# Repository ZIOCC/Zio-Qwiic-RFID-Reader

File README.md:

# Zio Qwiic RFID Reader (MFRC522)

> ###### About Zio
> Zio is a new line of open sourced, compact, and grid layout boards, fully integrated for Arduino and Qwiic ecosystem. Designed ideally for wearables, robotics, small-space limitations or other on the go projects. Check out other awesome Zio products [here](https://www.smart-prototyping.com/Zio)

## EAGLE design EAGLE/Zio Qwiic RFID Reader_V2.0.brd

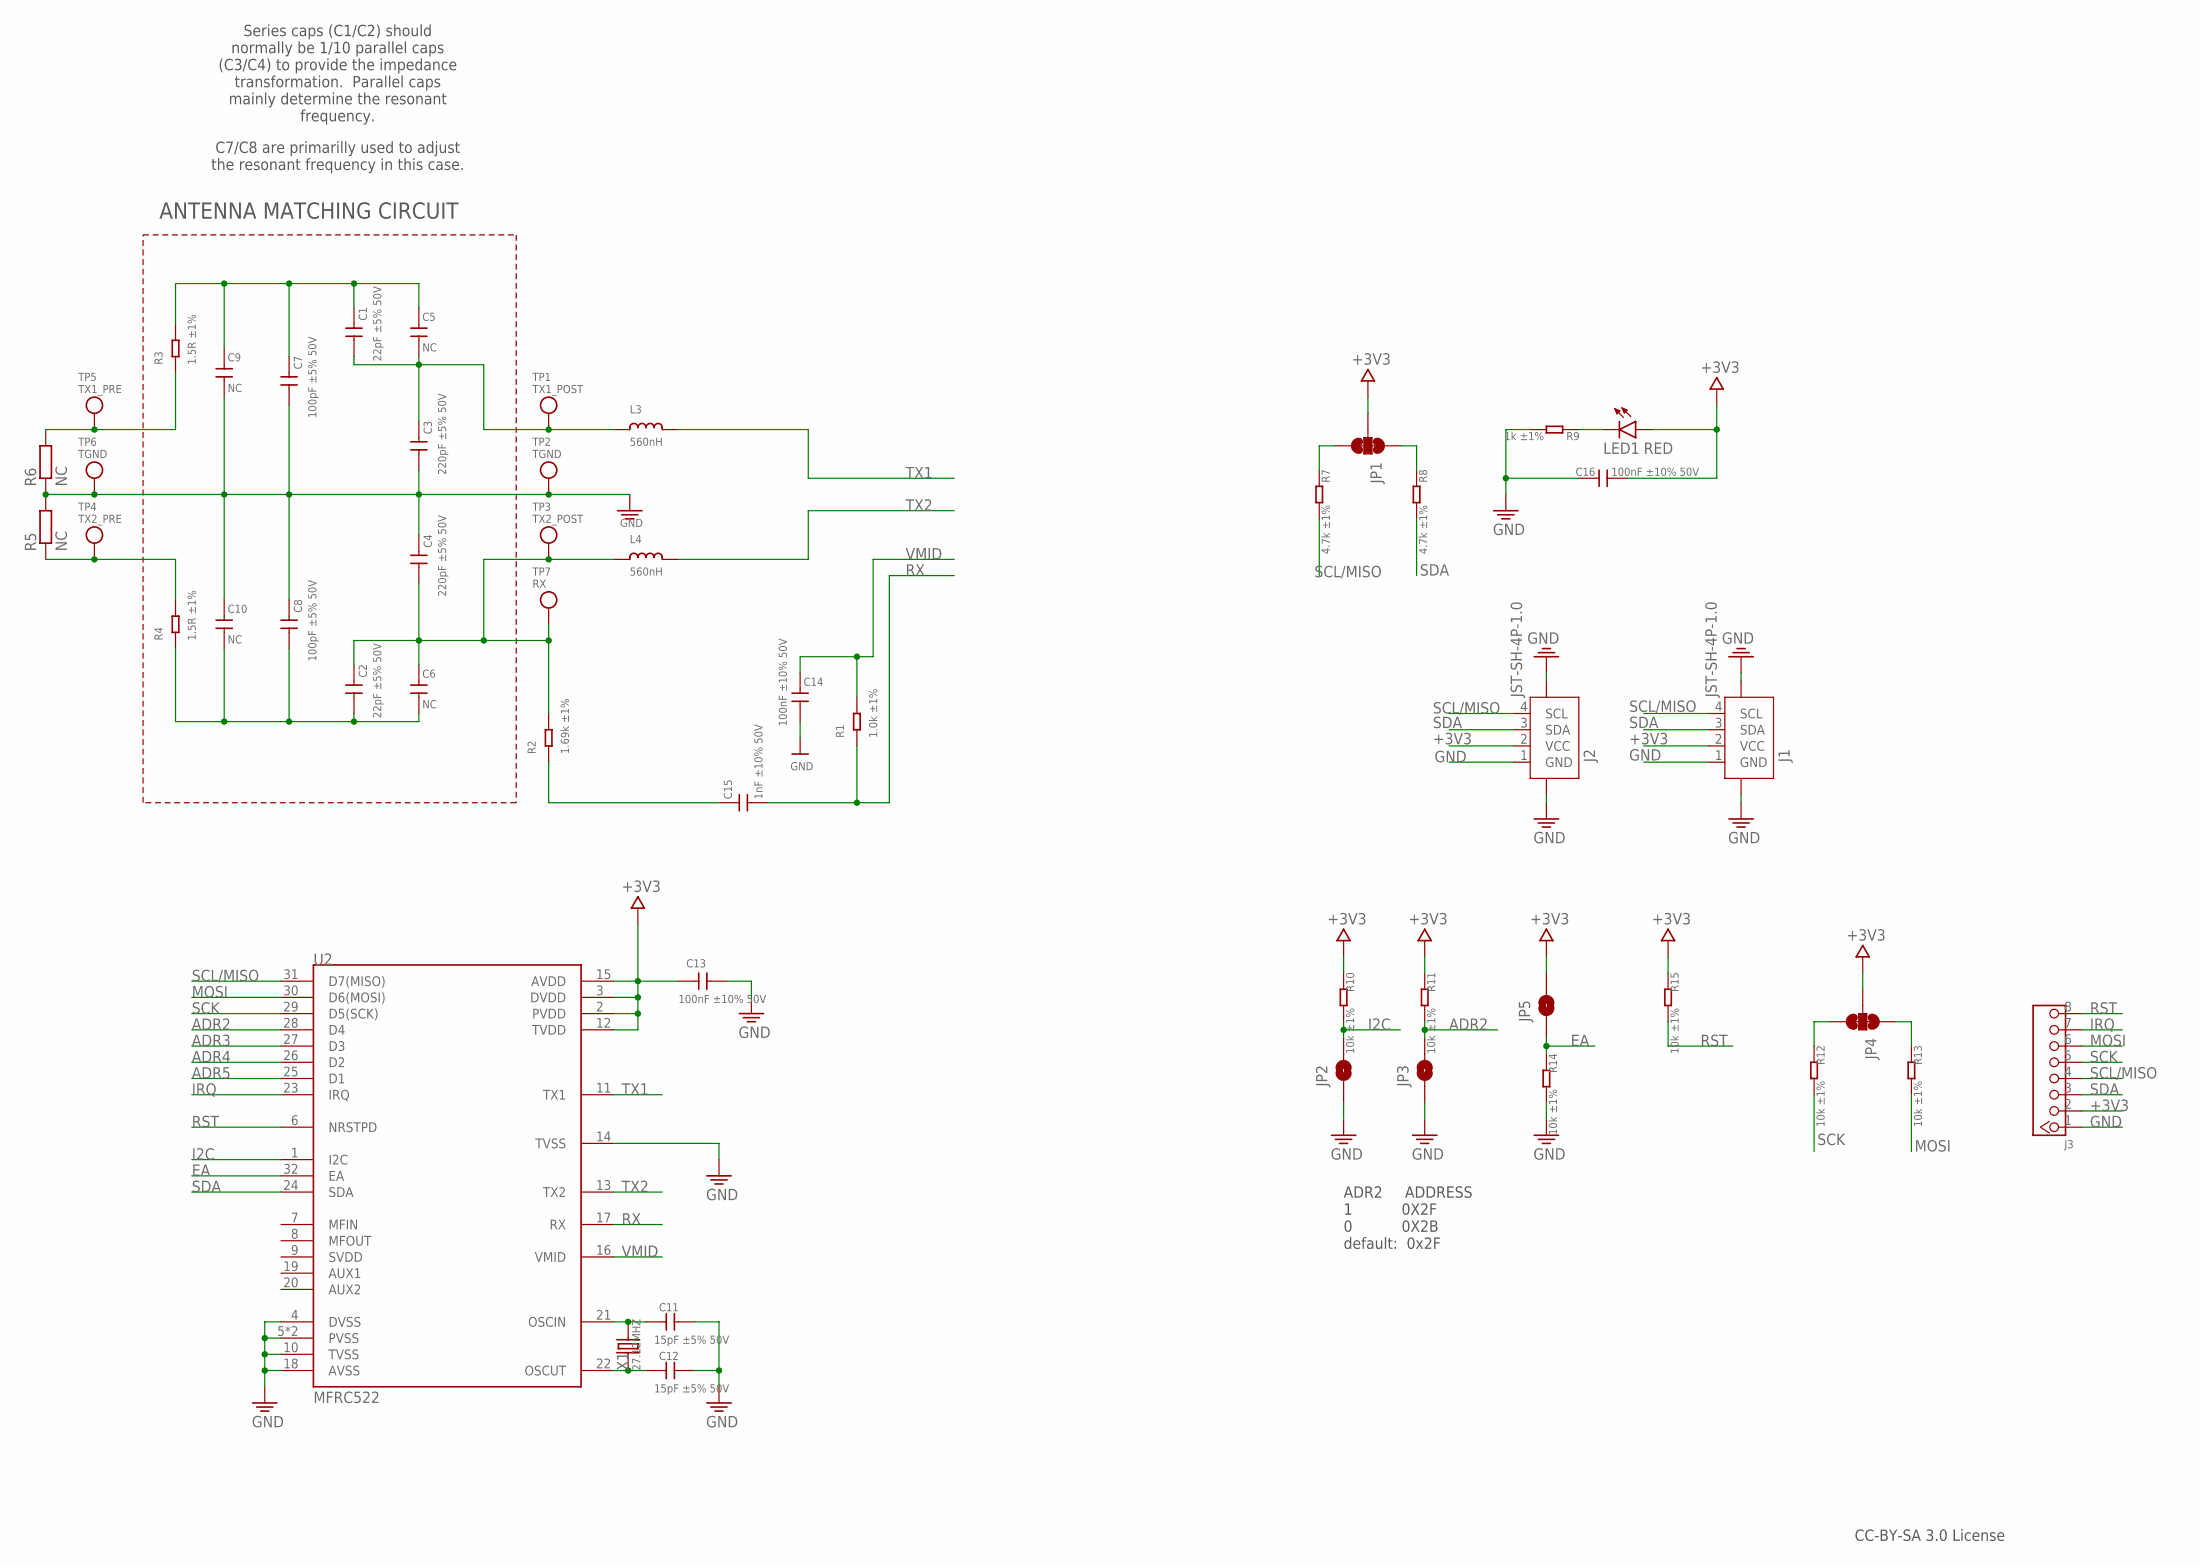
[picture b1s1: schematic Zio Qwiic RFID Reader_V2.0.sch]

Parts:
C1, C2: 22pF ±5% 50V; C0603
C3, C4: 220pF ±5% 50V; C0603
C5, C6, C9, C10: NC; C0603
C7, C8: 100pF ±5% 50V; C0603
C11, C12: 15pF ±5% 50V; C0603
C13, C14, C16: 100nF ±10% 50V; C0603
C15: 1nF ±10% 50V; C0603
J1, J2: JST-SH-4P-1.0; JST-SH-4P
J3: HEADER-8P-60/35MIL; 8P-2.54-60/35MIL
JP1, JP4: SMT-JUMPER_3_2-NC_TRACE
JP2, JP3, JP5: JUMPER-SMT_2_NC_PASTE_NOCREM; SMT-JUMPER_2_NC_PASTE_SILK_NOCREM
L3, L4: 560nH; 0805
LED1: RED; CHIP-LED0603
R1: 1.0k ±1%; R0603
R2: 1.69k ±1%; R0603
R3, R4: 1.5R ±1%; R0603
R5, R6: NC; R0201
R7, R8: 4.7k ±1%; R0603
R9: 1k ±1%; R0603
R10, R11, R12, R13, R14, R15: 10k ±1%; R0603
TP1: TX1_POST; TESTPOINT_ROUND_1MM
TP2, TP6: TGND; TESTPOINT_ROUND_1MM
TP3: TX2_POST; TESTPOINT_ROUND_1MM
TP4: TX2_PRE; TESTPOINT_ROUND_1MM
TP5: TX1_PRE; TESTPOINT_ROUND_1MM
TP7: RX; TESTPOINT_ROUND_1MM
U1: MFRC522; HVQFN32
X1: 27.12MHZ; HC49UP

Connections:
+3V3: C13.2, C16.2, J1.2 (VCC), J2.2 (VCC), J3.2, JP1.2, JP4.2, JP5.2, LED1.A, R10.1, R11.1, R15.1, U1.2 (PVDD), U1.3 (DVDD), U1.12 (TVDD), U1.15 (AVDD)
ADR2: JP3.2, R11.2, U1.28 (D4)
ADR3: U1.27 (D3)
ADR4: U1.26 (D2)
ADR5: U1.25 (D1)
EA: JP5.1, R14.1, U1.32 (EA)
GND: C3.2, C4.1, C7.2, C8.1, C9.2, C10.1, C11.1, C12.1, C13.1, C14.2, C16.1, J1.1 (GND), J1.NC1 (5), J1.NC2 (6), J2.1 (GND), J2.NC1 (5), J2.NC2 (6), J3.1, JP2.1, JP3.1, R5.2, R6.1, R9.2, R14.2, TP2.P$1, TP6.P$1, U1.4 (DVSS), U1.5 (PVSS), U1.10 (TVSS), U1.14 (TVSS), U1.18 (AVSS), U1.33 (PVSS)
I2C: JP2.2, R10.2, U1.1 (I2C)
IRQ: J3.7, U1.23 (IRQ)
MOSI: J3.6, R13.2, U1.30 (D6(MOSI))
unnamed: C12.2, U1.22 (OSCUT), X1.1
unnamed: C11.2, U1.21 (OSCIN), X1.2
unnamed: C1.2, C3.1, C5.2, L3.1, TP1.P$1
unnamed: R3.1, R6.2, TP5.P$1
unnamed: R4.2, R5.1, TP4.P$1
unnamed: JP1.3, R7.1
unnamed: C15.1, R2.1
unnamed: C2.1, C4.2, C6.1, L4.1, R2.2, TP3.P$1, TP7.P$1
unnamed: JP1.1, R8.1
unnamed: JP4.3, R12.1
unnamed: JP4.1, R13.1
unnamed: LED1.C, R9.1
RST: J3.8, R15.2, U1.6 (NRSTPD)
RX: C15.2, R1.1, U1.17 (RX)
SCK: J3.5, R12.2, U1.29 (D5(SCK))
SCL/MISO: J1.4 (SCL), J2.4 (SCL), J3.4, R7.2, U1.31 (D7(MISO))
SDA: J1.3 (SDA), J2.3 (SDA), J3.3, R8.2, U1.24 (SDA)
TX1: L3.2, U1.11 (TX1)
TX1_ANTENNA: C1.1, C5.1, C7.1, C9.1, R3.2
TX2: L4.2, U1.13 (TX2)
TX2_ANTENNA: C2.2, C6.2, C8.2, C10.2, R4.1
VMID: C14.1, R1.2, U1.16 (VMID)

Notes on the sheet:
ANTENNA MATCHING CIRCUIT
CC-BY-SA 3.0 License
Series caps (C1/C2) should normally be 1/10 parallel caps (C3/C4) to provide the impedance transformation. Parallel caps mainly determine the resonant frequency.
C7/C8 are primarilly used to adjust the resonant frequency in this case.
ADR2 ADDRESS 1 0X2F 0 0X2B default: 0x2F

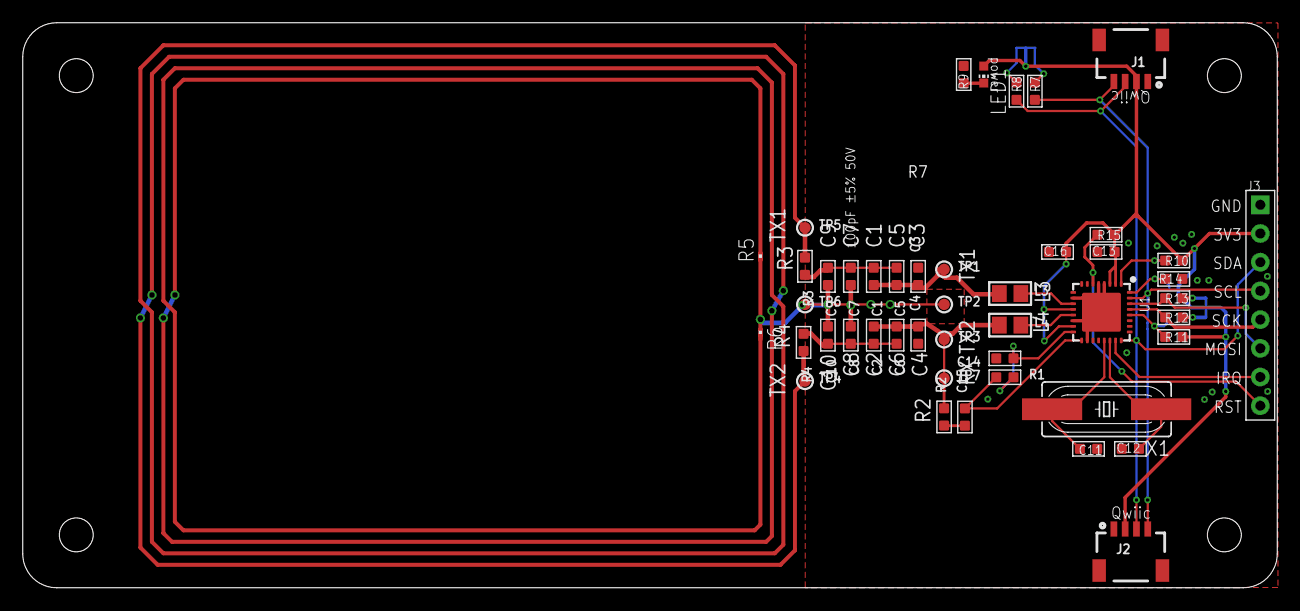
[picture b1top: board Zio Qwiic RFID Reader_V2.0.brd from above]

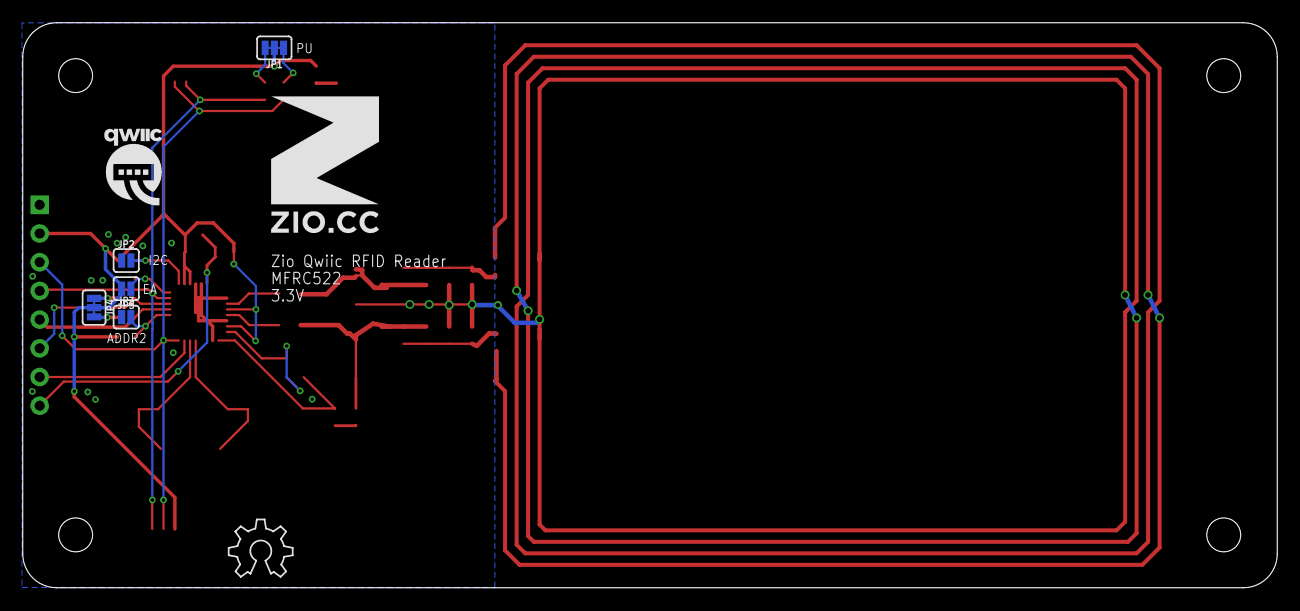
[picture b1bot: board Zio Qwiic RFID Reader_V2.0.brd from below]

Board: 2 copper layers, 111.0 x 50.0 mm, 54 parts (8 on the bottom side), 29 nets.

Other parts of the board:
U$7: 12MM
U$10: QWIIC-LOGO-MEDIUM
U$13: OSHW_6X200_NOTEXT
